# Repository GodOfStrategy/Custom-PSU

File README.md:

## About This Project

This project is my attempt at designing a fully programmable bench power supply from the ground up.

Most hobbyist power supplies are either simple fixed-voltage supplies or rely heavily on pre-built modules. I wanted to understand the entire system myself, from power conversion and feedback control to measurement, user interface, and digital regulation. The result is a custom-designed power supply capable of generating an adjustable output of approximately 0V to 30V at up to 5A from a standard 12V DC adapter.

The design combines modern switching power electronics with digital control, allowing the power supply to behave more like a commercial laboratory instrument than a traditional adjustable supply.

---

# Motivation
I love watching ElectroBOOM and he loves to blow up capacitors so I got some FOMO and needed a way to safely blow some capacitors up! (jk)
During electronics prototyping, I often found myself needing different voltages and current limits depending on the project being tested. Instead of purchasing a commercial bench supply, I decided to design one myself.

The primary objectives were:

- Wide adjustable voltage range
- Current limiting capability
- Digital control instead of analog potentiometers
- Real-time voltage and current monitoring
- Large and readable displays
- USB connectivity for future expansion
- Learning advanced power electronics in the process

This project was intended not only as a practical tool but also as a way to gain hands-on experience with high-power DC-DC converter design.

---

# Design Goals

| Parameter | Target |
|------------|------------|
| Input Voltage | 12V DC |
| Output Voltage | ~0V - 30V |
| Maximum Current | 5A |
| Maximum Power | 150W |
| Regulation Method | Digital |
| User Interface | Rotary Encoders |
| Display | LED 7-Segment Displays |
| Communication | USB |

---

# System Overview

The power supply can be divided into several major sections:

1. Power Input and Protection
2. Power Conversion
3. Measurement System
4. Control Electronics
5. User Interface

The overall concept is shown below:

```text
12V Adapter
     │
     ▼
Input Protection
     │
     ▼
Buck / Boost Power Stage
     │
     ▼
Current & Voltage Measurement
     │
     ▼
Microcontroller Control Loop
     │
     ├── DAC Voltage Control
     ├── Display Interface
     ├── USB Communication
     └── User Input
     │
     ▼
 Adjustable Output
     0V - 30V @ 5A
```

---

# Power Conversion

One of the biggest challenges in the project is that the output voltage can be significantly higher than the input voltage.

Since the system is powered from a 12V adapter but needs to produce up to 30V at the output, a boost-capable power architecture is required.

The power stage is built around:

- LM5116 synchronous controller
- LM51231 synchronous boost controller
- High-current MOSFETs
- Shielded power inductors
- Precision current sensing

These components allow efficient conversion while minimizing heat generation.

The theoretical maximum output power was designed around:

```text
30V × 5A = 150W
```

making the supply suitable for most low- and medium-power electronics projects.

---

# Digital Control

Rather than using traditional potentiometers for voltage adjustment, this design uses a digital control system.

At the center of the project is an:

### ATmega328P

The microcontroller is responsible for:

- Reading user inputs
- Monitoring output voltage/current
- Controlling the output setpoint
- Driving the displays
- Managing system behavior

This allows settings to be consistent, repeatable, and expandable through software.

---

# Digital Voltage Regulation

Output voltage adjustment is performed using an MCP4725 12-bit DAC.

Instead of physically changing a potentiometer, the microcontroller generates a precise reference voltage that controls the converter feedback loop.

This approach enables:

- Fine output adjustment
- Accurate calibration
- Software-defined voltage control
- Future preset storage functionality

---

# Measurement and Monitoring

A bench power supply is only useful if the user can see exactly what is happening at the output.

To achieve this, the design includes an INA260 power monitor.

The INA260 measures:

- Output voltage
- Output current
- Output power

These measurements are available digitally through I²C and can be displayed directly to the user.

This reduces complexity while improving overall measurement accuracy.

---

# User Interface

The user interface was designed to feel similar to a commercial bench power supply.

## Input Controls

Two EC11 rotary encoders are used for:

- Voltage adjustment
- Current limit adjustment
- Menu navigation

Rotary encoders were chosen because they allow precise control without requiring multiple buttons or large potentiometers.

---

## Display System

The display system uses:

- 3 × MAX7219 display drivers
- 3 × large seven-segment LED displays

The intended display arrangement is:

### Display 1
Output Voltage

### Display 2
Output Current

### Display 3
Additional information such as:

- Power
- Current limits
- Menu settings
- Calibration data

The large displays were selected for visibility and ease of use from across a workbench.

---

# Connectivity

USB support is provided through a CH340G USB-to-UART converter.

This opens possibilities for:

- Firmware updates
- Serial debugging
- Data logging
- Computer-based monitoring
- Future remote control functionality

While not essential for operation, USB greatly expands the potential capabilities of the power supply.

---

# Protection Features

Reliability and safety were important considerations throughout the design.

The PSU includes:

- TVS diodes for surge suppression
- Polyfuse protection
- Current monitoring
- Precision current sensing
- Input filtering
- Noise suppression through ferrite beads

These features help protect both the power supply and any connected loads.

---

# What I Learned

This project exposed me to several advanced engineering topics, including:

- High-power DC-DC converter design
- Switching power supply compensation
- Current sensing techniques
- Digital control of analog systems
- PCB layout for power electronics
- Mixed-signal design
- Microcontroller firmware integration

---

# Final Thoughts

This project was designed as much for learning as it was for practicality. The goal was not simply to build another adjustable power supply, but to understand how a modern digitally controlled laboratory PSU is designed from the component level upward.

From the switching converters and measurement circuitry to the display system and firmware-controlled regulation, every major subsystem was intentionally designed and integrated into a single platform. The result is a custom programmable bench power supply capable of delivering up to 30V and 5A while providing a user experience similar to that of commercial laboratory equipment.
This is what my Schematics are: 
This is how my assembled PCB is supposed to look like:
My PCB 2 Schematics: 
My second PCB design:
My second PCB assembled Look:
How my Case and the finished product is supposed to look:

BOM:
# Bill of Materials (BOM)

| Designator(s) | Component | Quantity | Description | Source |
|--------------|------------|----------|-------------|---------|
| U1 | ATmega328P | 1 | Main microcontroller | Robu.in |
| U2 | CH340G | 1 | USB-to-UART interface | JLCPCB |
| U3 | MCP4725A0T-E/CH | 1 | 12-bit DAC for voltage control | Robu.in |
| U4 | INA260 | 1 | Voltage, current, and power monitor | JLCPCB |
| U5 | LM5116MHX | 1 | Synchronous buck controller | JLCPCB |
| U6 | LM51231QRGRRQ1 | 1 | Synchronous boost controller | JLCPCB |
| U11 | TPS54202DDCR | 1 | Auxiliary buck regulator | Robu.in |
| U8, U9, U10 | MAX7219M/TR | 3 | LED display drivers | JLCPCB |
| Q1, Q2, Q5, Q6 | SI7850DP | 4 | Power MOSFETs | Robu.in |
| Q3, Q4 | BSC014N06NS | 2 | Boost stage power MOSFETs | JLCPCB |
| L1 | 10 µH Inductor | 1 | Power filtering inductor | JLCPCB |
| L2 | 8.2 µH Inductor | 1 | Main buck converter inductor | JLCPCB |
| L3 | 6 µH Inductor | 1 | Boost converter inductor | JLCPCB |
| D1, D2 | SMBJ33A | 2 | TVS surge protection diodes | JLCPCB |
| D3 | CMPD2003 | 1 | Signal diode | JLCPCB |
| U7 | 2920L500/30GR | 1 | Resettable polyfuse | JLCPCB |
| DC1 | DC-005-A200 | 1 | DC barrel jack input | JLCPCB |
| J1 | USB Type-C Receptacle | 1 | USB connectivity | JLCPCB |
| J2, J4, J5 | 2×6 Pin Header | 3 | Expansion/programming headers | JLCPCB |
| J3 | 2-Pin Screw Terminal | 1 | PSU output connector | JLCPCB |
| J6, J7 | 1×3 Pin Header | 2 | Auxiliary headers | JLCPCB |
| Y1 | 16 MHz Crystal | 1 | ATmega328P clock source | JLCPCB |
| Y2 | 12 MHz Crystal | 1 | CH340G clock source | JLCPCB |
| SW1, SW2 | EC11 Rotary Encoder | 2 | User input controls | JLCPCB |
| SW3 | RS601A-1020013BB | 1 | Power/control switch | JLCPCB |
| LED1, LED2, LED3 | SR420561N | 3 | Seven-segment LED displays | JLCPCB |
| FB1 | Ferrite Bead | 1 | EMI suppression | JLCPCB |
| FID1, FID2, FID3 | Fiducials | 3 | PCB assembly alignment markers | JLCPCB |
| All Capacitors (C1–C41) | Mixed Values | 41 | Decoupling, filtering, compensation, and bulk storage capacitors | JLCPCB |
| All Resistors (R1–R31) | Mixed Values | 31 | Feedback, sensing, compensation, pull-ups, and current measurement | JLCPCB |

---

## Custom Components Procured Separately

| Component | Quantity | Source | Product Link |
|------------|----------|---------|-------------|
| SI7850DP MOSFET | 4 | Robu.in | https://robu.in/product/si7850dp-xblw-60v-30a-34-7w-25m%CF%8910v15a-1-2v250ua-1-n-channel-dfn-8l5x6-mosfets-rohs/ |
| ATmega328-PU | 2 | Robu.in | https://robu.in/product/atmega328-pu-microchip-8-bit-microcontroller-avr-atmega-family-atmega328-series-microcontrollers-20-mhz-1-kb-32-kb/ |
| TPS54202DDCR | 2 | Robu.in | https://robu.in/product/tps54202ddcr-texas-instruments-step-down-type-adjustable-2a-4-5v28v-sot-23-6-dc-dc-converters-rohs/ |
| MCP4725A0T-E/CH | 2 | Robu.in | https://robu.in/product/mcp4725a0t-e-ch-microchip-tech-6us-i2c-2lsb-2-7v5-5v-12-sot-23-6-digital-to-analog-converters-dac-rohs/ |
|24V Adapter DC||1||Amazon||https://www.amazon.in/Shapure-Adapter-Purifier-Converter-Warranty/dp/B09B2QC5DG/ref=sr_1_3?crid=3QK3BS6AOUQGM&dib=eyJ2IjoiMSJ9.z5ReBGRa2kELup8lCjC9Z7aZuXaMR9FyGI59wlhLV9FMg2_YwJbg-YGzdv5CkLi6aMEvTBOCxrnhVwAJYl9CR0xRAVpL0OUx6rveTMBEYwV-mfzAP5N47bOksV7mx_d-q-OOJnq-4oGTEWsJdjWCeMDMi4jjhaLBmjWdgFatwtrf7cfvZgy4Otxe9zJH1EiS2ARtcMDir2YeDqLj4Z12yNAxxOiE48LgPSrV04CDX3I.cCkpyZVzpHKVdfWwwR1xSpiSNuYyTB53HvmkVU3qjbI&dib_tag=se&keywords=24V+dc+adapter&qid=1791563890&sprefix=24v+dc+adapt%2Caps%2C314&sr=8-3|

---

## Manufacturing Cost

| Item | Cost |
|--------|--------:|
| PCB Fabrication | $4.00 |
| PCB Assembly (PCBA) | $165.19 |
| Shipping | $18.54 |
| **Total JLCPCB Cost** | **$187.73** |

---

## External Component Cost

| Source | Cost |
|---------|------:|
| Robu.in Components | $17.69 |
|Amazon.in||$4.6|

---

## Project Totals

| Category | Quantity |
|-----------|---------:|
| Integrated Circuits | 10 |
| MOSFETs | 6 |
| Diodes | 3 |
| Inductors | 3 |
| Crystals | 2 |
| Connectors | 7 |
| Displays | 3 |
| Rotary Encoders | 2 |
| Switches | 1 |
| Capacitors | 41 |
| Resistors | 31 |
| Protection Devices | 3 |

---

# Final Project Cost

| Cost Component | Total |
|----------------|--------:|
| JLCPCB Manufacturing (PCB + PCBA + Shipping) | $187.73 |
| Robu.in Components | $17.69 |
|Amazon.in||4.6$|
| **Total Project Cost** | **$210.02** |

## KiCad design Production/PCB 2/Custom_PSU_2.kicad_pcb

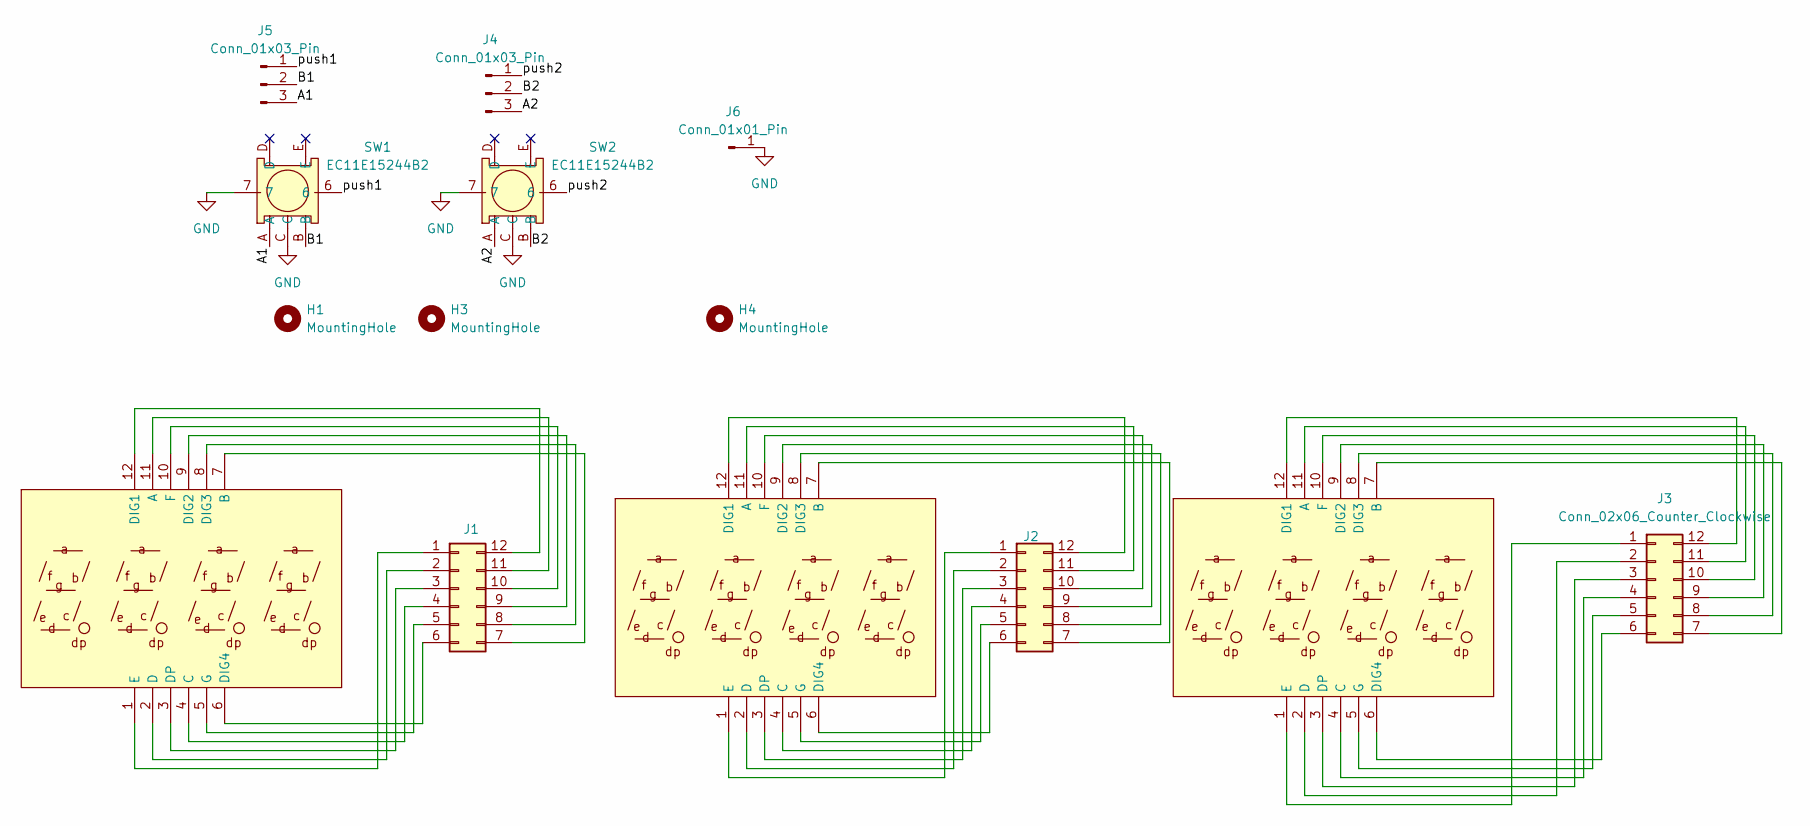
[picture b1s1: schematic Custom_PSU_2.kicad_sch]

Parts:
H1, H3, H4: MountingHole; MountingHole_3.2mm_M3_ISO7380
J1, J2, J3: Conn_02x06_Counter_Clockwise; PinHeader_2x06_P2.54mm_Vertical
J4, J5: Conn_01x03_Pin; PinHeader_1x03_P2.54mm_Vertical
J6: Conn_01x01_Pin; PinHeader_1x01_P2.54mm_Vertical
LED1, LED2, LED3: SR420561N; LED-SEG-TH_12P-L50.3-W19.0-P2.54-S15.24-BL; MPN SR420561N; LCSC Part C109200
SW1, SW2: EC11E15244B2; SW-TH_EC11XXXXXXXX; MPN EC11E15244B2; LCSC Part C470754

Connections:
/A1: J5.3, SW1.A
/A2: J4.3, SW2.A
/B1: J5.2, SW1.B
/B2: J4.2, SW2.B
/push1: J5.1, SW1.6
/push2: J4.1, SW2.6
GND: J6.1, SW1.7, SW1.C, SW2.7, SW2.C
unnamed: J1.1, LED1.1 (E)
unnamed: J1.2, LED1.2 (D)
unnamed: J1.3, LED1.3 (DP)
unnamed: J1.4, LED1.4 (C)
unnamed: J1.5, LED1.5 (G)
unnamed: J1.6, LED1.6 (DIG4)
unnamed: J1.7, LED1.7 (B)
unnamed: J1.8, LED1.8 (DIG3)
unnamed: J1.9, LED1.9 (DIG2)
unnamed: J1.10, LED1.10 (F)
unnamed: J1.11, LED1.11 (A)
unnamed: J1.12, LED1.12 (DIG1)
unnamed: J2.1, LED2.1 (E)
unnamed: J2.2, LED2.2 (D)
unnamed: J2.3, LED2.3 (DP)
unnamed: J2.4, LED2.4 (C)
unnamed: J2.5, LED2.5 (G)
unnamed: J2.6, LED2.6 (DIG4)
unnamed: J2.7, LED2.7 (B)
unnamed: J2.8, LED2.8 (DIG3)
unnamed: J2.9, LED2.9 (DIG2)
unnamed: J2.10, LED2.10 (F)
unnamed: J2.11, LED2.11 (A)
unnamed: J2.12, LED2.12 (DIG1)
unnamed: J3.1, LED3.1 (E)
unnamed: J3.2, LED3.2 (D)
unnamed: J3.3, LED3.3 (DP)
unnamed: J3.4, LED3.4 (C)
unnamed: J3.5, LED3.5 (G)
unnamed: J3.6, LED3.6 (DIG4)
unnamed: J3.7, LED3.7 (B)
unnamed: J3.8, LED3.8 (DIG3)
unnamed: J3.9, LED3.9 (DIG2)
unnamed: J3.10, LED3.10 (F)
unnamed: J3.11, LED3.11 (A)
unnamed: J3.12, LED3.12 (DIG1)

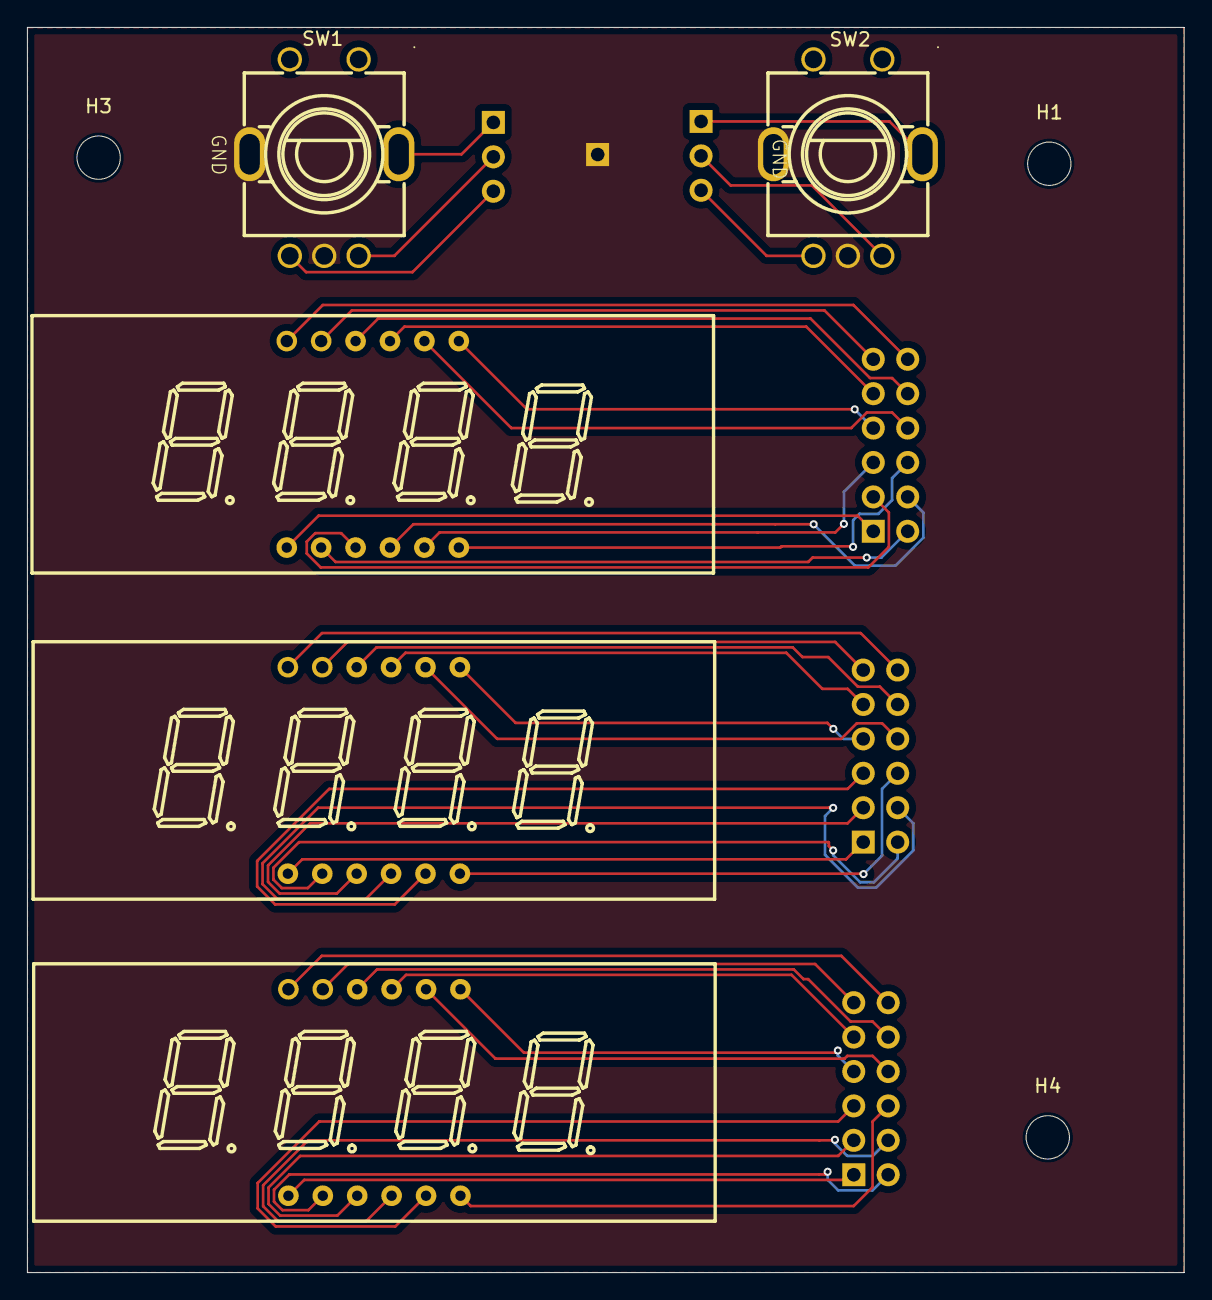
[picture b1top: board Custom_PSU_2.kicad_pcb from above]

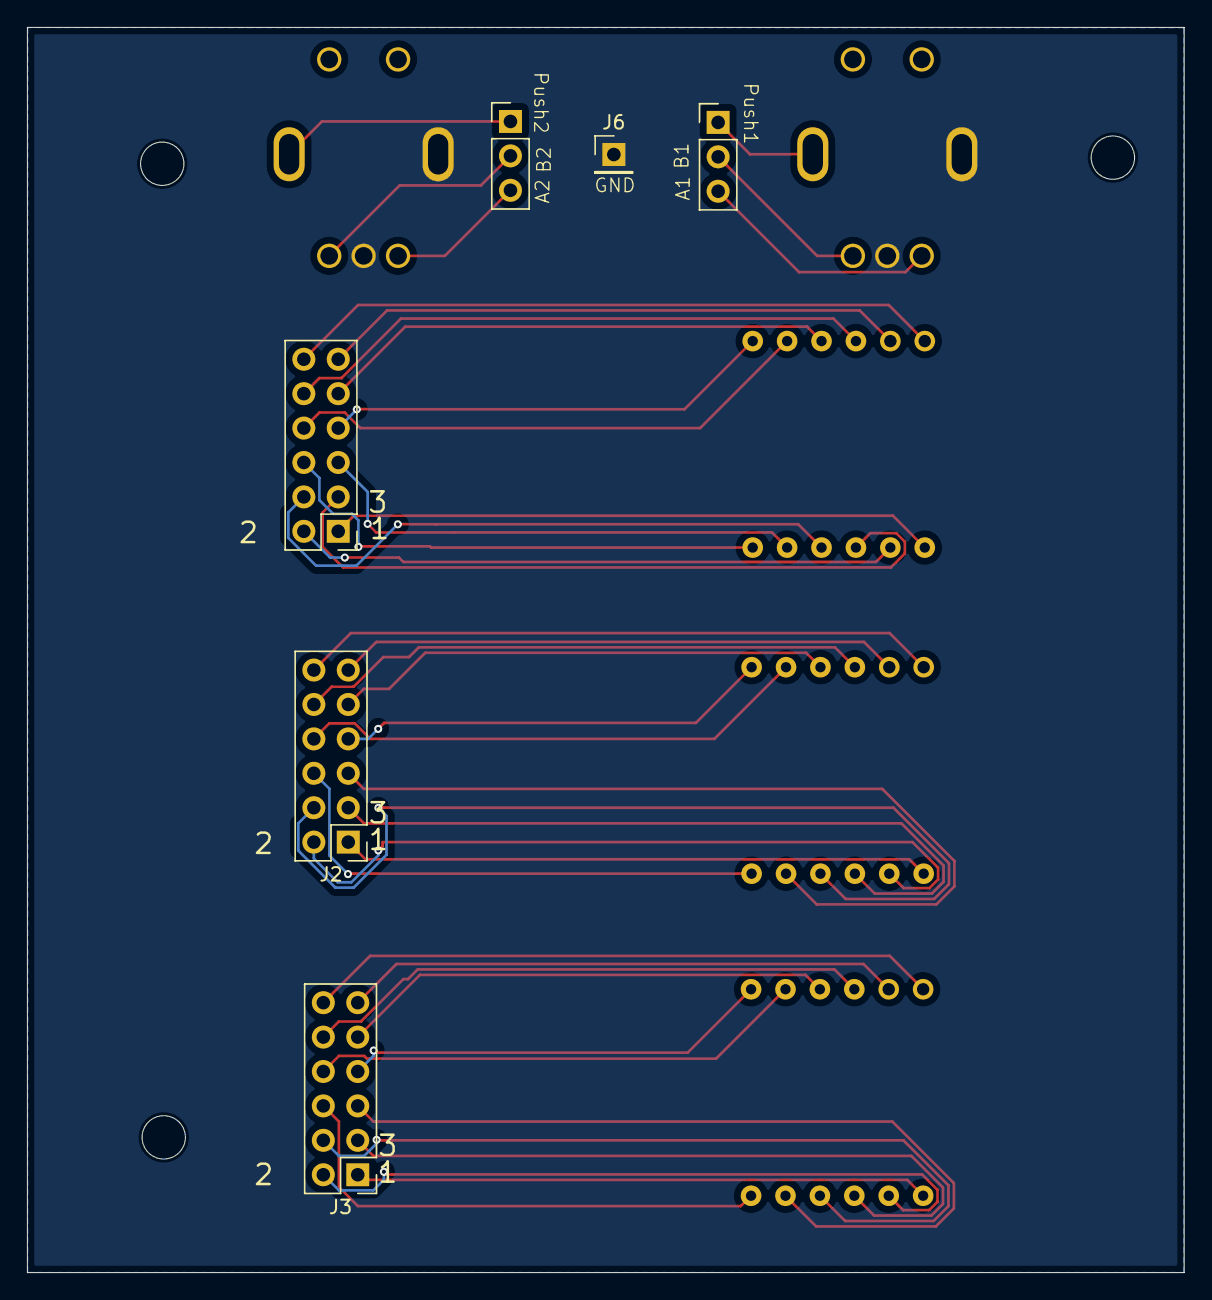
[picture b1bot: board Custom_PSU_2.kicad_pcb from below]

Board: 2 copper layers, 85.4 x 91.9 mm, 14 parts (6 on the bottom side), 43 nets.

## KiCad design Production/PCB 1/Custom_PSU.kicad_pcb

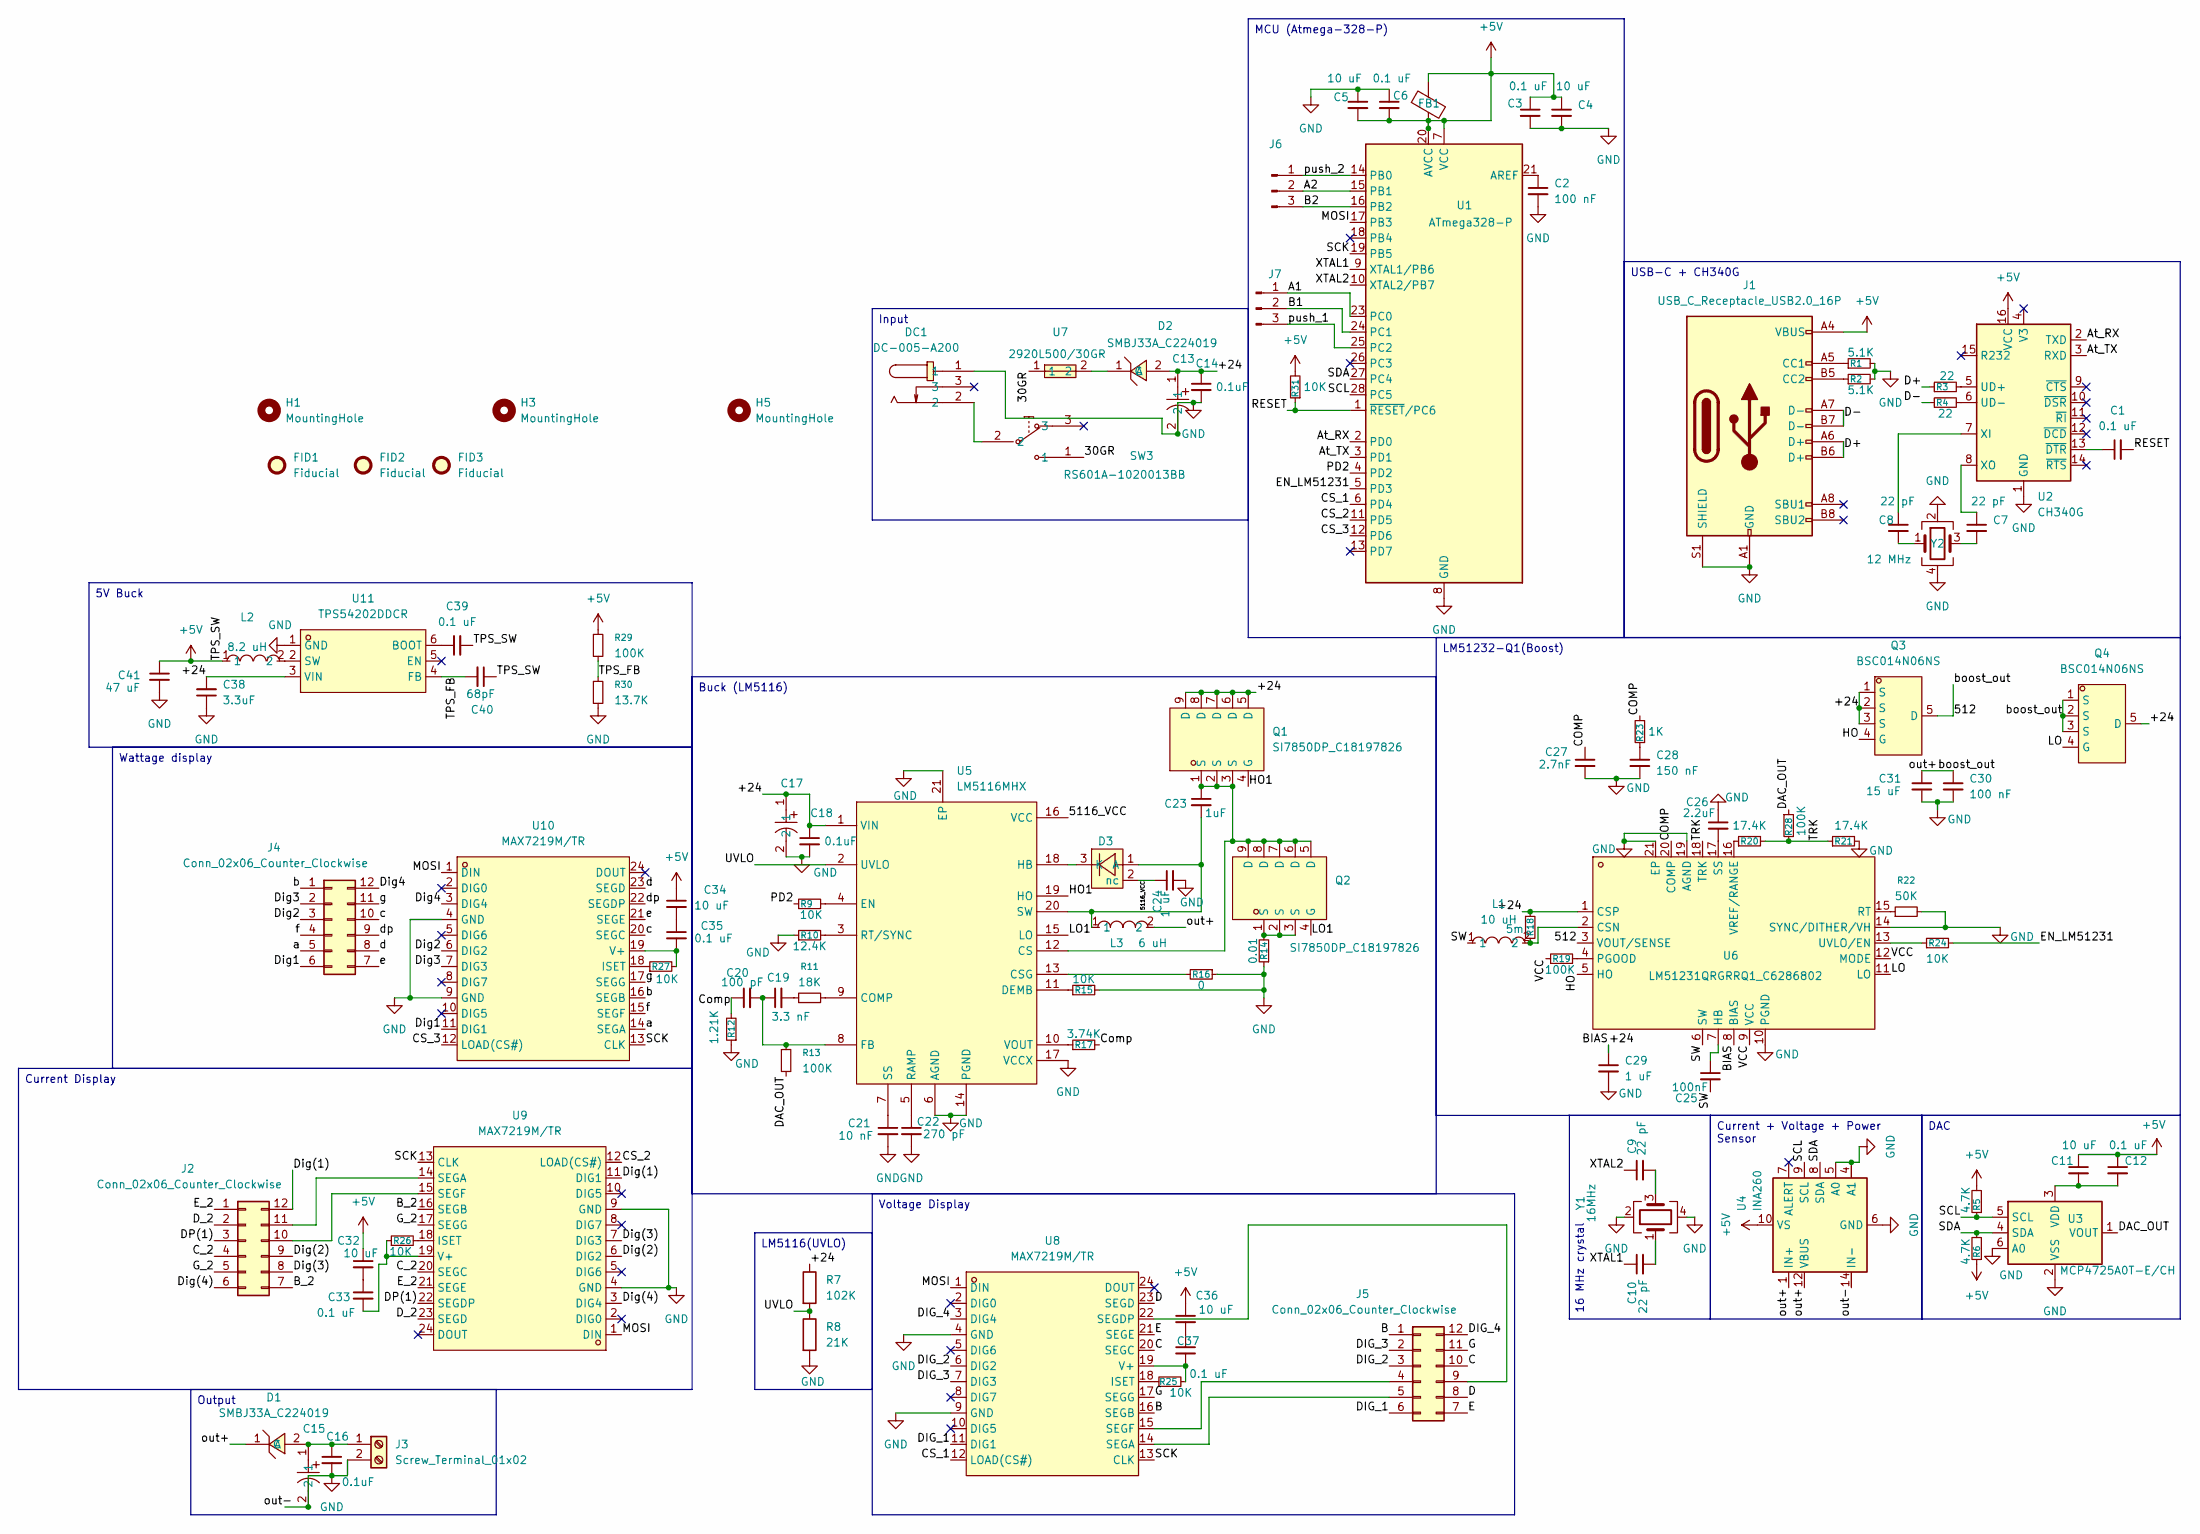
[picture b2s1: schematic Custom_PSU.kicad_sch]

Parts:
C1, C3, C5, C12, C33, C35, C37, C39: 0.1 uF; C_0805_2012Metric
C2, C30: 100 nF; C_0805_2012Metric
C4, C6, C11, C32, C34, C36: 10 uF; C_0603_1608Metric
C7, C8, C9, C10: 22 pF; C_0805_2012Metric
C13, C15, C17: EEVTG1H471M; CP_Elec_10x12.5; MPN EEVTG1H471M; LCSC Part C401988
C14, C16, C18: 0.1uF; C_0805_2012Metric
C19: 3.3 nF; C_0603_1608Metric
C20: 100 pF; C_0603_1608Metric
C21: 10 nF; C_0805_2012Metric
C22: 270 pF; C_0603_1608Metric
C23: 1uF; C_0603_1608Metric
C24, C29: 1 uF; C_0603_1608Metric
C25: 100nF; C_0805_2012Metric
C26: 2.2uF; C_0805_2012Metric
C27: 2.7nF; C_0603_1608Metric
C28: 150 nF; C_0603_1608Metric
C31: 15 uF; C_0805_2012Metric
C38: 3.3uF; C_0603_1608Metric
C40: 68pF; C_0402_1005Metric
C41: 47 uF; C_0603_1608Metric
D1, D2: SMBJ33A_C224019; SMB_L4.6-W3.6-LS5.3-RD; MPN SMBJ33A; LCSC Part C224019
D3: CMPD2003 TR PBFREE; SOT-23-3_L2.9-W1.3-P1.90-LS2.3-BR; MPN CMPD2003 TR PBFREE; LCSC Part C17378378
DC1: DC-005-A200; DC-IN-TH_DC-005-A200; MPN DC-005-A200; LCSC Part C720557
FB1: FerriteBead; L_0805_2012Metric
FID1, FID2, FID3: Fiducial; Fiducial_1mm_Mask2mm
H1, H3, H5: MountingHole; MountingHole_3.2mm_M3_ISO7380
J1: USB_C_Receptacle_USB2.0_16P; USB_C_Receptacle_HCTL_HC-TYPE-C-16P-01A
J2, J4, J5: Conn_02x06_Counter_Clockwise; PinHeader_2x06_P2.54mm_Vertical
J3: Screw_Terminal_01x02; TerminalBlock_Xinya_XY308-2.54-2P_1x02_P2.54mm_Horizontal
J6, J7: Conn_01x03_Pin; PinHeader_1x03_P2.54mm_Vertical
L1: 10 uH; IND-SMD_L5.2-W5.2_MCW-0530; MPN SMMS0530-100M; LCSC Part C181721
L2: 8.2 uH; IND-SMD_L7.0-W6.6_FXL0630; MPN FXL0630-8R2-M; LCSC Part C167222
L3: 6 uH; IND-SMD_L6.7-W6.7_CDRH6D26HPNP-4R7PC; MPN CDRH6D28NP-6R0NC; LCSC Part C879413
Q1, Q2: SI7850DP_C18197826; PDFN-8_L5.8-W5.0-P1.27-LS6.0-BL; MPN SI7850DP; LCSC Part C18197826
Q3, Q4: BSC014N06NS; POWERVDFN-8_L6.2-W5.2-P1.27-LS6.0-BL; MPN BSC014N06NS; LCSC Part C113391
R1, R2: 5.1K; R_0805_2012Metric
R3, R4: 22; R_0402_1005Metric
R5, R6: 4.7K; R_0805_2012Metric
R7: 102K; R_0805_2012Metric
R8: 21K; R_0805_2012Metric
R9, R15, R24, R25, R26, R27, R31: 10K; R_0805_2012Metric
R10: 12.4K; R_0805_2012Metric
R11: 18K; R_0805_2012Metric
R12: 1.21K; R_0805_2012Metric
R13, R19, R28: 100K; R_0805_2012Metric
R14: 0.01; R_1206_3216Metric
R16: 0; R_1206_3216Metric
R17: 3.74K; R_0805_2012Metric
R18: 5m; R_1206_3216Metric
R20, R21: 17.4K; R_0805_2012Metric
R22: 50K; R_0805_2012Metric
R23: 1K; R_0805_2012Metric
R29: 100K; R_0402_1005Metric
R30: 13.7K; R_0603_1608Metric
SW3: RS601A-1020013BB; SW-TH_RS601A-1020013BB; MPN RS601A-1020013BB; LCSC Part C5124216
U1: ATmega328-P; DIP-28_W7.62mm
U2: CH340G; SOIC-16_3.9x9.9mm_P1.27mm
U3: MCP4725A0T-E/CH; SOT-23-6
U4: INA260; TSSOP-16_4.4x5mm_P0.65mm
U5: LM5116MHX; HTSSOP-20_L6.5-W4.4-P0.65-LS6.4-BL-EP; MPN LM5116MHX/NOPB; LCSC Part C13755
U6: LM51231QRGRRQ1_C6286802; VQFN-20_L3.5-W3.5-P0.50-BL-EP2.1; MPN LM51231QRGRRQ1; LCSC Part C6286802
U7: 2920L500/30GR; F2920; MPN 2920L500/30GR; LCSC Part C19078763
U8, U9, U10: MAX7219M/TR; SOP-24_L15.4-W7.5-P1.27-LS10.4-BL; MPN MAX7219M/TR; LCSC Part C6705351
U11: TPS54202DDCR; SOT-23-6_L2.9-W1.6-P0.95-LS2.8-BL; MPN TPS54202DDCR; LCSC Part C191884
Y1: 16MHz; Crystal_SMD_3225-4Pin_3.2x2.5mm
Y2: 12 MHz; Crystal_SMD_3225-4Pin_3.2x2.5mm

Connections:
+5V: C3.1, C4.1, C5.2, C6.2, C11.1, C12.1, C32.1, C34.1, C36.1, C39.2, C40.1, C41.1, FB1.1, FB1.2, J1.A4 (VBUS), J1.A9 (VBUS), J1.B4 (VBUS), J1.B9 (VBUS), L2.1, R5.2, R6.1, R29.1, R31.2, U1.7 (VCC), U1.20 (AVCC), U2.16 (VCC), U4.10 (VS)
/30GR: SW3.1, U7.1
/5116_VCC: C24.1, D3.2 (nc), U5.16 (VCC)
/+24: C13.1, C14.1, C17.1, C18.1, C29.1, C38.2, D2.2 (A), Q1.5 (D), Q1.6 (D), Q1.7 (D), Q1.8 (D), Q1.9 (D), Q3.1 (S), Q3.2 (S), Q3.3 (S), Q4.5 (D), R7.1, R18.1, U5.1 (VIN), U6.1 (CSP), U6.8 (BIAS), U11.3 (VIN)
/A1: J7.1, U1.23 (PC0)
/A2: J6.2, U1.15 (PB1)
/At_RX: U1.2 (PD0), U2.2 (TXD)
/At_TX: U1.3 (PD1), U2.3 (RXD)
/B: J5.1, U8.16 (SEGB)
/B1: J7.2, U1.24 (PC1)
/B2: J6.3, U1.16 (PB2)
/B_2: J2.7, U9.16 (SEGB)
/C: J5.10, U8.20 (SEGC)
/COMP: C27.1, R23.2, U6.20 (COMP)
/CS_1: U1.6 (PD4), U8.12 (LOAD(CS#))
/CS_2: U1.11 (PD5), U9.12 (LOAD(CS#))
/CS_3: U1.12 (PD6), U10.12 (LOAD(CS#))
/C_2: J2.4, U9.20 (SEGC)
/Comp: C20.1, R12.2, R17.2
/D: J5.8, U8.23 (SEGD)
/D+: J1.A6 (D+), J1.B6 (D+), R3.1
/D-: J1.A7 (D-), J1.B7 (D-), R4.1
/DAC_OUT: R13.2, R28.1, U3.1 (VOUT)
/DIG_1: J5.6, U8.11 (DIG1)
/DIG_2: J5.3, U8.6 (DIG2)
/DIG_3: J5.2, U8.7 (DIG3)
/DIG_4: J5.12, U8.3 (DIG4)
/DP(1): J2.3, U9.22 (SEGDP)
/D_2: J2.2, U9.23 (SEGD)
/Dig1: J4.6, U10.11 (DIG1)
/Dig2: J4.3, U10.6 (DIG2)
/Dig3: J4.2, U10.7 (DIG3)
/Dig4: J4.12, U10.3 (DIG4)
/Dig(1): J2.12, U9.11 (DIG1)
/Dig(2): J2.9, U9.6 (DIG2)
/Dig(3): J2.8, U9.7 (DIG3)
/Dig(4): J2.6, U9.3 (DIG4)
/E: J5.7, U8.21 (SEGE)
/EN_LM51231: R24.2, U1.5 (PD3)
/E_2: J2.1, U9.21 (SEGE)
/G: J5.11, U8.17 (SEGG)
/G_2: J2.5, U9.17 (SEGG)
/HO: Q3.4 (G), U6.5 (HO)
/HO1: Q1.4 (G), U5.19 (HO)
/LO: Q4.4 (G), U6.11 (LO)
/LO1: Q2.4 (G), U5.15 (LO)
/MOSI: U1.17 (PB3), U8.1 (DIN), U9.1 (DIN), U10.1 (DIN)
/PD2: R9.1, U1.4 (PD2)
/RESET: C1.2, R31.1, U1.1 (~RESET/PC6)
/SCK: U1.19 (PB5), U8.13 (CLK), U9.13 (CLK), U10.13 (CLK)
/SCL: R5.1, U1.28 (PC5), U3.5 (SCL), U4.9 (SCL)
/SDA: R6.2, U1.27 (PC4), U3.4 (SDA), U4.8 (SDA)
/SW: C25.2, L1.1, U6.6 (SW)
/TPS_FB: C40.2, R29.2, R30.1, U11.4 (FB)
/TRK: R20.2, R21.1, R28.2, U6.18 (TRK)
/UVLO: R7.2, R8.1, U5.2 (UVLO)
/VCC: R19.1, U6.9 (VCC), U6.12 (MODE)
/XTAL1: C10.1, U1.9 (XTAL1/PB6)
/XTAL2: C9.1, U1.10 (XTAL2/PB7)
/a: J4.5, U10.14 (SEGA)
/b: J4.1, U10.16 (SEGB)
/c: J4.10, U10.20 (SEGC)
/d: J4.8, U10.23 (SEGD)
/dp: J4.9, U10.22 (SEGDP)
/e: J4.7, U10.21 (SEGE)
/f: J4.4, U10.15 (SEGF)
/g: J4.11, U10.17 (SEGG)
/push_1: J7.3, U1.25 (PC2)
/push_2: J6.1, U1.14 (PB0)
GND: C2.2, C3.2, C4.2, C5.1, C6.1, C13.2, C14.2, C15.2, C16.2, C17.2, C18.2, C21.2, C22.2, C24.2, C26.1, C27.2, C28.2, C29.2, C30.2, C31.2, C38.1, C41.2, DC1.1, J1.A1 (GND), J1.A12 (GND), J1.B1 (GND), J1.B12 (GND), J1.S1 (SHIELD), J3.2, R1.2, R2.2, R8.2, R10.1, R12.1, R14.1, R15.2, R16.1, R21.2, R22.2, R30.2, U1.8 (GND), U1.22 (GND), U2.1 (GND), U3.2 (VSS), U3.6 (A0), U4.4 (A1), U4.5 (A0), U4.6 (GND), U4.11 (GND), U4.14 (IN-), U4.15 (IN-), U4.16 (IN-), U5.6 (AGND), U5.14 (PGND), U5.17 (VCCX), U5.21 (EP), U6.10 (PGND), U6.14 (SYNC/DITHER/VH), U6.19 (AGND), U6.21 (EP), U8.4 (GND), U8.9 (GND), U9.4 (GND), U9.9 (GND), U10.4 (GND), U10.9 (GND), U11.1 (GND), Y1.2, Y1.4, Y2.2, Y2.4
unnamed: C7.2, Y2.3
unnamed: C8.2, Y2.1
unnamed: C9.2, Y1.3
unnamed: C10.2, Y1.1
unnamed: C19.2, R11.1
unnamed: C28.1, R23.1
unnamed: C32.2, C33.1
unnamed: C34.2, C35.1
unnamed: C36.2, C37.1
unnamed: C15.1, C16.1, D1.2 (A), J3.1
unnamed: D2.1 (C), U7.2
unnamed: C23.2, D3.1 (A), L3.1, U5.20 (SW)
unnamed: D3.3 (K), U5.18 (HB)
unnamed: DC1.2, SW3.2
unnamed: J1.A5 (CC1), R1.1
unnamed: J1.B5 (CC2), R2.1
unnamed: J2.10, U9.15 (SEGF)
unnamed: J2.11, U9.14 (SEGA)
unnamed: J5.4, U8.15 (SEGF)
unnamed: J5.5, U8.14 (SEGA)
unnamed: J5.9, U8.22 (SEGDP)
unnamed: Q2.1 (S), Q2.2 (S), Q2.3 (S), R14.2
unnamed: C2.1, U1.21 (AREF)
unnamed: R3.2, U2.5 (UD+)
unnamed: R4.2, U2.6 (UD-)
unnamed: C8.1, U2.7 (XI)
unnamed: C7.1, U2.8 (XO)
unnamed: C1.1, U2.13 (~DTR)
unnamed: C11.2, C12.2, U3.3 (VDD)
unnamed: R11.2, U5.9 (COMP)
unnamed: C23.1, Q1.1 (S), Q1.2 (S), Q1.3 (S), Q2.5 (D), Q2.6 (D), Q2.7 (D), Q2.8 (D), Q2.9 (D), U5.12 (CS)
unnamed: R16.2, U5.13 (CSG)
unnamed: R15.1, U5.11 (DEMB)
unnamed: R9.2, U5.4 (EN)
unnamed: C19.1, C20.2, R13.1, U5.8 (FB)
unnamed: C22.1, U5.5 (RAMP)
unnamed: R10.2, U5.3 (RT/SYNC)
unnamed: C21.1, U5.7 (SS)
unnamed: R17.1, U5.10 (VOUT)
unnamed: L1.2, R18.2, U6.2 (CSN)
unnamed: C25.1, U6.7 (HB)
unnamed: R19.2, U6.4 (PGOOD)
unnamed: R22.1, U6.15 (RT)
unnamed: C26.2, U6.17 (SS)
unnamed: R24.1, U6.13 (UVLO/EN)
unnamed: R20.1, U6.16 (VREF/RANGE)
unnamed: R25.1, U8.18 (ISET)
unnamed: C37.2, R25.2, U8.19 (V+)
unnamed: R26.2, U9.18 (ISET)
unnamed: C33.2, R26.1, U9.19 (V+)
unnamed: R27.1, U10.18 (ISET)
unnamed: C35.2, R27.2, U10.19 (V+)
unnamed: C39.1, U11.6 (BOOT)
unnamed: L2.2, U11.2 (SW)

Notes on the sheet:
Buck (LM5116)
Voltage Display
Current Display
LM5116(UVLO)
Wattage display
16 MHz crystal
LM51232-Q1(Boost)
USB-C + CH340G
MCU (Atmega-328-P)
Current + Voltage + Power Sensor
5V Buck
Input
Output
DAC

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
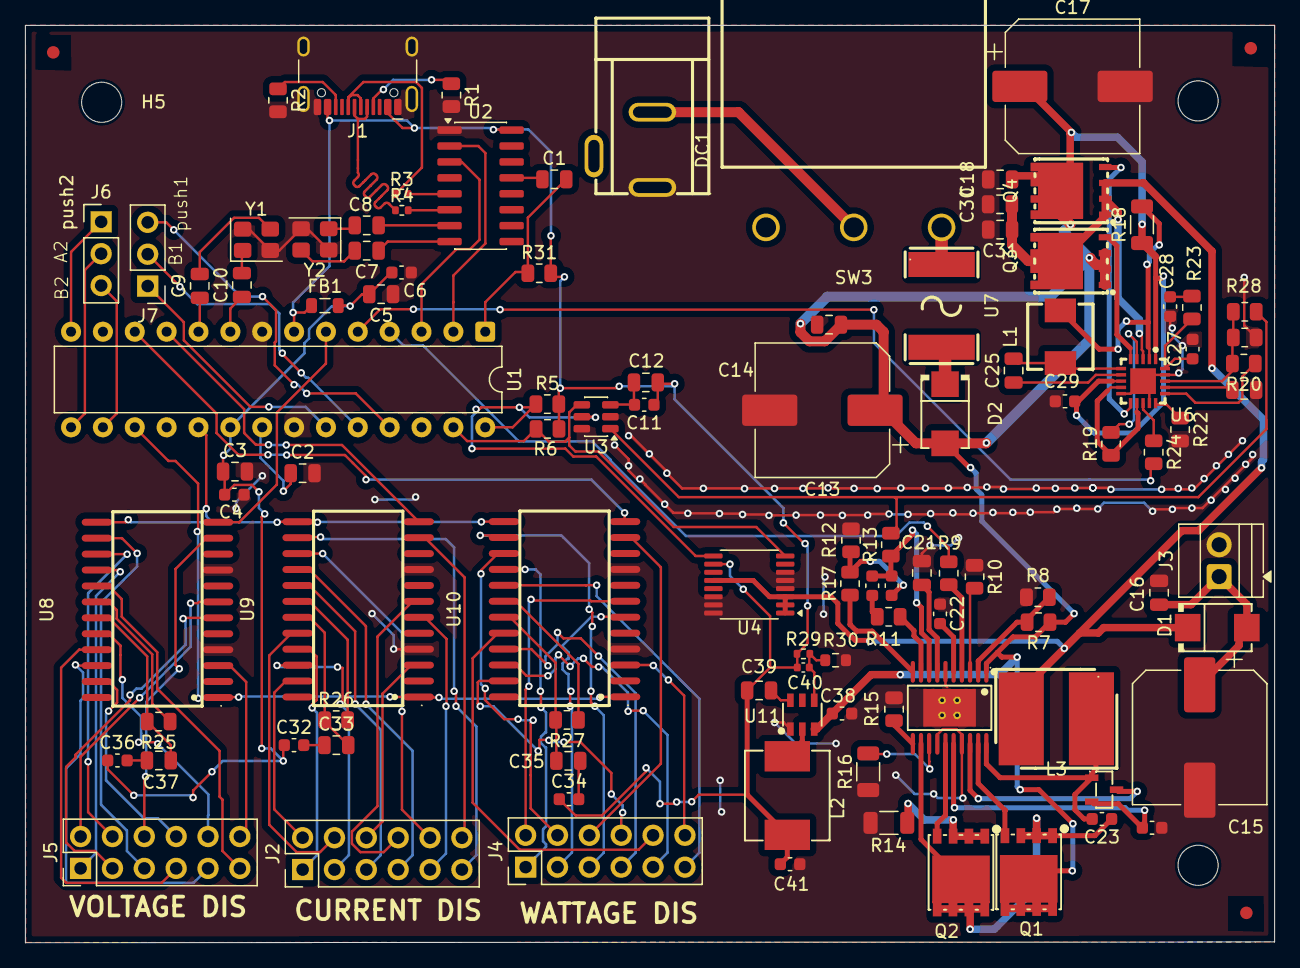
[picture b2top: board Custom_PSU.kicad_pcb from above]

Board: 2 copper layers, 99.6 x 73.1 mm, 111 parts (0 on the bottom side), 126 nets.
